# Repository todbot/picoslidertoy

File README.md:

# picoslidertoy

## Table of contents 

- [picoslidertoy](#picoslidertoy)
  - [Table of contents](#table-of-contents)
  - [What is it?](#what-is-it)
  - [Variants](#variants)
  - [Parts needed](#parts-needed)
  - [Soldering components](#soldering-components)
  - [Firmware installation / Installing apps](#firmware-installation--installing-apps)
    - [CircuitPython apps](#circuitpython-apps)
    - [Ready-to-go UF2 file](#ready-to-go-uf2-file)
    - [Installing by hand](#installing-by-hand)
  - [Why?](#why)
    - [What makes it special?](#what-makes-it-special)
    - [Press links](#press-links)

## What is it?
[picoslidertoy](https://github.com/todbot/picoslidertoy) is a touch-sensitive 
control surface that uses 24 GPIO pins of the Raspberry Pi Pico to provide:

- three linear sliders
- two rotary sliders
- nine buttons
- all capacitive touch 

It also includes a cutout for a reverse-mounted SSD1306 I2C OLED display. The Raspberry Pi Pico SMD mounts to the back of the board to provide a clean look for the touch surface.  The entire PCB is 165 mm x 76 mm (6.5" x 3.0").

The picoslidertoy can be a USB MIDI control surface, a USB Macropad keyboard with "analog" controls, or even a USB gamepad.  It can be programmed in [CircuitPython](https://circuitpython.org/) and [`touchio`](https://docs.circuitpython.org/en/latest/shared-bindings/touchio/index.html) or Arduino with my [`TouchyTouch library`](https://github.com/todbot/TouchyTouch).  Several example firmware apps are provided.

## Variants

There are two versions of the picoslidertoy available:

- black PCB -- production version with proper alignment of the cutout for standard 0.96" I2C OLED, comes with all SMD resistors soldered down  Note: the silkscreen on the back has a typo, saying `0.91" I2C OLED`. 

- green PCB -- prototype version with no components soldered down and where the I2C OLED display cutout is a little off. Still usable, or mount the display on the face. 

There is also a nice minimal 3d-printable enclosure available in the github repo (and visible in the photos above).  You really want a case for capacitive touch projects like this to reduce spurious readings. 

## Parts needed

In addition to the [picoslidertoy PCB](https://www.tindie.com/products/todbot/picoslidertoy-capsense-controller-for-pico/), you will need:

- Raspberry Pi Pico 
  - Must be w/ castellated pads & w/o headers,  ([like this](https://amzn.to/4d0KFZC))
  - For USB-C, consider this [USB-C 16 MB Pico clone](https://www.aliexpress.us/item/3256804731684211.html)
  - **(NOTE: NOT the Pico2, since its RP2350 chip has a hardware error)**

- I2C OLED display SSD1306 
   - 0.96" 128 x 64 pixels, in white
   - Pins must be in GND,VCC,SCL,SDA order 
   - Prefer the 27.5 mm wide displays over the 25 mm wide ones ([one example](https://amzn.to/3KDmy73))

- (If you have a green proto one, you will also need 24 x 1M 0603 resistors and 2 x 10k 0603 resistors)

- [3d printed case](./enclosure/picoslidertoy_case.stl) or M2.5 standoffs/screws or some other feet

## Soldering components

- **Pico**  -- the Pico is soldered down surface-mount style, using its castellated pads. 
  [This video soldering a Pico on picotouch](https://github.com/todbot/picotouch?tab=readme-ov-file#how-to-solder-the-pico) is how I do it for this board too.  It's technically surface-mount soldering, 
  but the pads are bigger than most through-hole pads and easy to solder to. 
  Note that Pico clones that don't have castellated pads like the real Pico will
  not work. 
  ([Youtube video with Pico SMD soldering tips](https://www.youtube.com/watch?v=dW9LiOq3Dso "Pico SMD soldering"))

- **OLED Display** -- the display can either be mounted on the front (especially easy if your display's pins
  come pre-soldered) or from the back (my preference).  If mounting from the back, you first need to 
  desolder the 4-pin header on the display and mount a new 4-pin header "reverse" so that pins stick up
  from the front of the display. The main header body is still on the back of the display. 
  (The video below hopefully makes this clearer).  When soldering, do one pin first and check alignment,
  then solder the rest of the pins. Finish up by trimming the excess header pins. 
  ([Youtube video with picoslidertoy soldering tips](https://www.youtube.com/watch?v=zxt3xpre2Vg))

## Firmware installation / Installing apps

### CircuitPython apps

These are the apps currently available 
- [hwtest](https://github.com/todbot/picoslidertoy/blob/main/circuitpython/hwtest/code.py)
    -- a simple on/off test of the touch sensors, no display needed. Use serial REPL to see results

- [hwtest display](https://github.com/todbot/picoslidertoy/blob/main/circuitpython/hwtest_display/code.py) -- like `hwtest` but also outputs simple feedback via the display
 
- [midi_sliders](https://github.com/todbot/picoslidertoy/blob/main/circuitpython/midi_sliders/) -- MIDI controller where the sliders emit CCs and the buttons send NoteOn/NoteOffs

If you've never used a Pico or CircuitPython, there are several ways to put code on it. 
The two main ways I'll present here are:

- Ready-to-go UF2 file in "Releases" 
- Installing by hand:  CircuitPython, code.py, libraries 

### Ready-to-go UF2 file

Steps to install a UF2 file:

- Download a ready-to-go UF2 file from the [Releases section](https://github.com/todbot/picoslidertoy/releases) section
- Hold the BOOTSEL button on the picoslidertoy's Pico while plugging it into your computer
- Copy the UF2 file to the "RPI-RP2" Pico bootloader drive 
- Wait for a bit, then app is running!

In general, I'll try to make UF2 files available in the [Releases section](https://github.com/todbot/picoslidertoy/releases) for the different apps.

### Installing by hand 

Steps to install by hand: 

- Download this repo, either with a `git clone` or clicking on "Code / Download ZIP"
- Download the latest CircuitPython UF2 for Pico at https://circuitpython.org/board/raspberry_pi_pico/
- Install the CircuitPython UF2 (like in the above UF2 steps)
- Wait for CircuitPython to come up and present a CIRCUITPY drive
- Copy the files of the picoslidertoy app in question to CIRCUITPY:

  e.g. for `midi_sliders`, copy `code.py`, `slider_display.py`, `touchslider.py` to CIRCUITPY
  ```
  cp circuitpython/midi_sliders/* /Volumes/CIRCUITPY  # (if macos)
  ```
   
- Install CircuitPython libraries onto Pico

    If you have Python on your computer you can do:
    ```
    pip3 install circup
    circup install adafruit_midi adafruit_displayio_ssd1306 adafruit_hid
    ```
    Otherwise, download the [CircuitPython Libraries Bundle](https://circuitpython.org/libraries)
    and copy over the `adafruit_midi`, `adafruit_displayio_ssd1306` and `adafruit_hid` libraries to
    the `CIRCUITPY/lib` folder on the Pico.

## Why?

I wanted a way to experiment with linear and rotary touch sliders.  I made some [touchwheels](https://github.com/todbot/touchwheels) to give away for Hackaday Supercon 2023 and they were popular. I wanted a larger playground for experimenting with these controls. 

### What makes it special?

The 24 capacitive touch sensors are read directly by the Pico, either via CircuitPython's `touchio` library or the `TouchyTouch` Arduino library.  No external touch chip needed.  I think that's really cool!  Getting an "analog" value out of the three touch sensors that make up a linear or rotary touch slider is fairly simple but there are some tricks I'm developing to make the values stable.

picoslidertoy is also completely open source with schematic files in KiCad and software in CircuitPython and Arduino.

### Press links

- [Adafruit Show-N-Tell Live show 10 Apr 2024](https://www.youtube.com/live/9aliKuS8NTw?si=FC51cfeyoLF2YsNm&t=1055)
- [Hackster.io 11 Apr 2024 article](https://www.hackster.io/news/tod-kurt-s-picoslidertoy-delivers-25-capacitive-touch-inputs-to-a-raspberry-pi-pico-with-sliders-368dca30f01c)

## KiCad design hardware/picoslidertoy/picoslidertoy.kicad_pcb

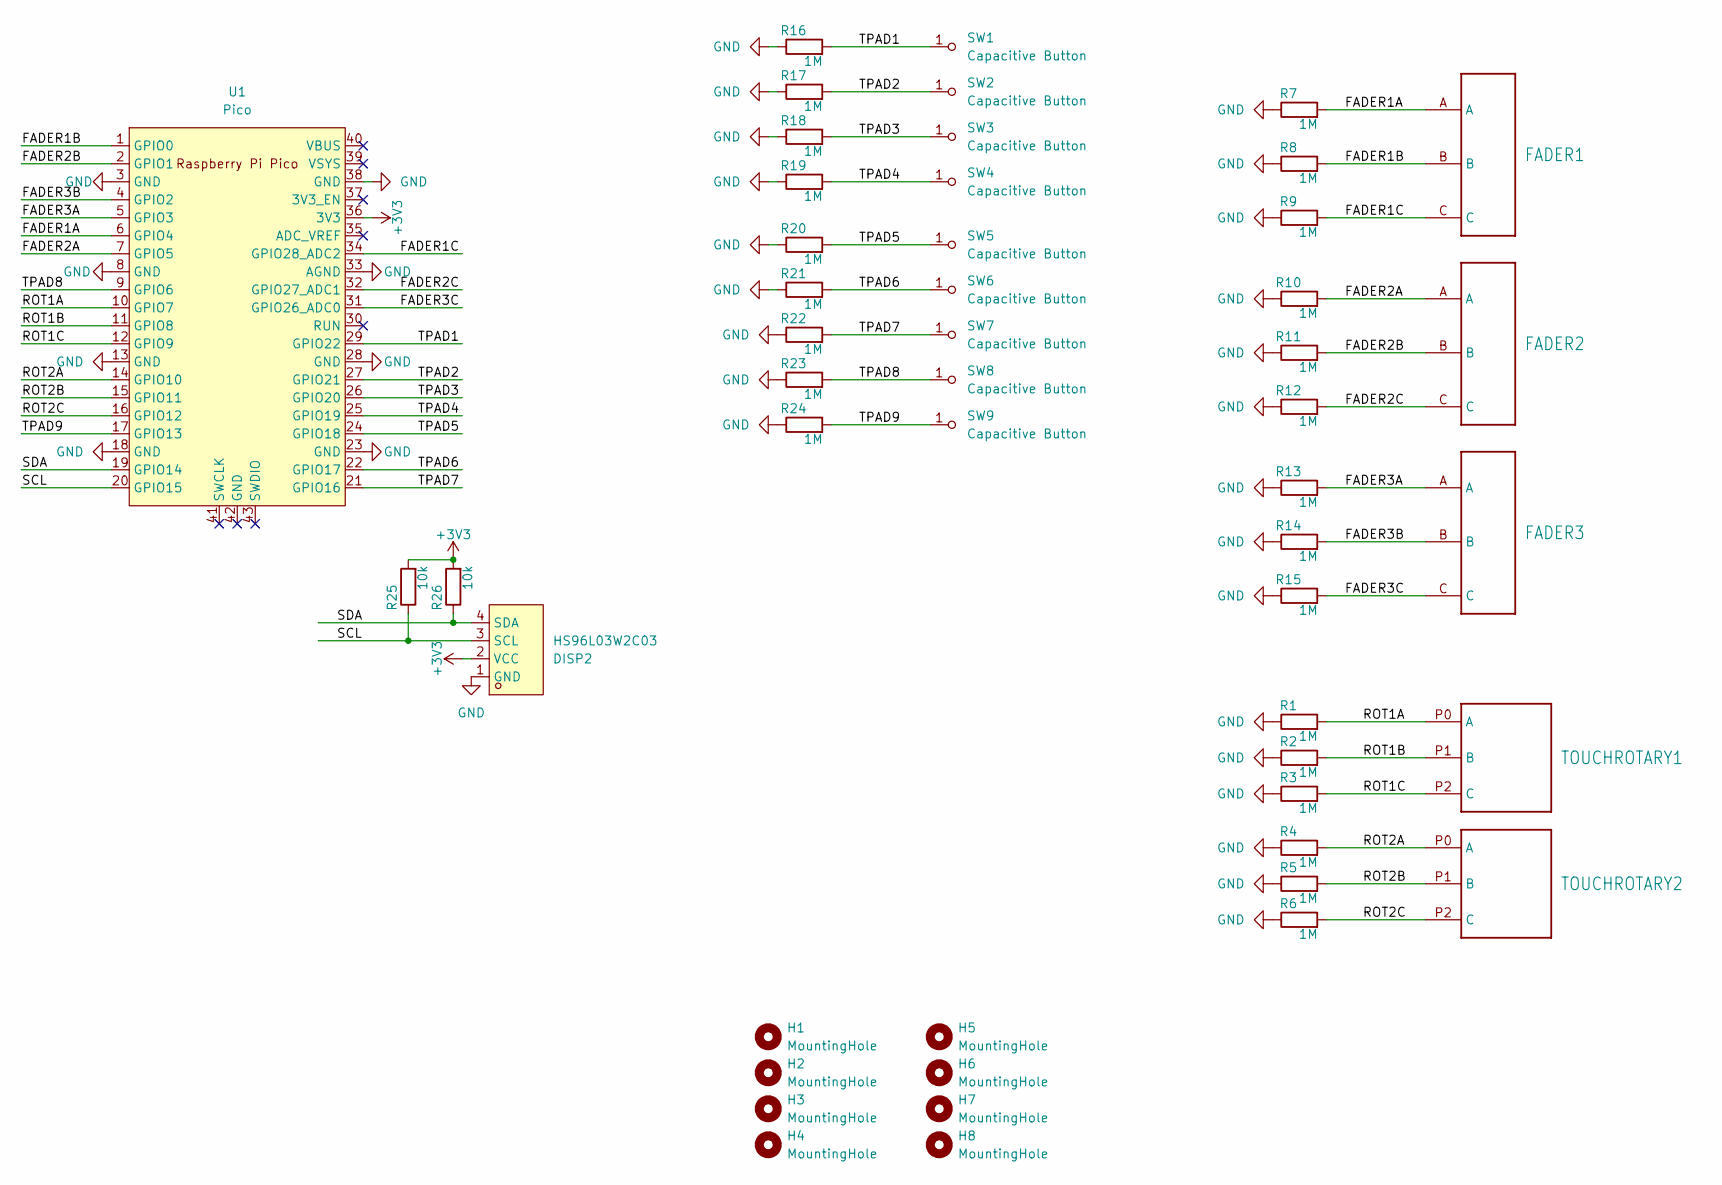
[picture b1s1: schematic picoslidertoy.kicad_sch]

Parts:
DISP2: HS96L03W2C03; OLED-TH_under_fixed_L27.8-W27.2-P2.54_C9900033791; LCSC Part C5248080
FADER1, FADER2, FADER3: TOUCHSLIDER3_8x40B
H1, H2: MountingHole; MountingHole_2.7mm_M2.5_ISO14580
H3, H4: MountingHole; MountingHole_2.7mm_M2.5
H5, H7, H8: MountingHole; MountingHole_2.5mm
H6: MountingHole; MountingHole_2.7mm
R1, R2, R3, R4, R5, R6, R7, R8, R9, R10, R11, R12, R13, R14, R15, R16, R17, R18, R19, R20, R21, R22, R23, R24: 1M; R_0603_1608Metric
R25, R26: 10k; R_0603_1608Metric
SW1, SW2, SW3, SW4, SW5, SW6, SW7, SW8, SW9: Capacitive Button; Pad-CapacitiveTouch
TOUCHROTARY1, TOUCHROTARY2: TOUCHROTARY1B
U1: Pico; RPi_Pico_SMD

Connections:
+3V3: DISP2.2 (VCC), R25.2, R26.2, U1.36 (3V3); also elsewhere on the board
/FADER1A: FADER1.A, R7.2, U1.6 (GPIO4)
/FADER1B: FADER1.B, R8.2, U1.1 (GPIO0)
/FADER1C: FADER1.C, R9.2, U1.34 (GPIO28_ADC2)
/FADER2A: FADER2.A, R10.2, U1.7 (GPIO5)
/FADER2B: FADER2.B, R11.2, U1.2 (GPIO1)
/FADER2C: FADER2.C, R12.2, U1.32 (GPIO27_ADC1)
/FADER3A: FADER3.A, R13.2, U1.5 (GPIO3)
/FADER3B: FADER3.B, R14.2, U1.4 (GPIO2)
/FADER3C: FADER3.C, R15.2, U1.31 (GPIO26_ADC0)
/ROT1A: R1.2, TOUCHROTARY1.P0 (A), U1.10 (GPIO7)
/ROT1B: R2.2, TOUCHROTARY1.P1 (B), U1.11 (GPIO8)
/ROT1C: R3.2, TOUCHROTARY1.P2 (C), U1.12 (GPIO9)
/ROT2A: R4.2, TOUCHROTARY2.P0 (A), U1.14 (GPIO10)
/ROT2B: R5.2, TOUCHROTARY2.P1 (B), U1.15 (GPIO11)
/ROT2C: R6.2, TOUCHROTARY2.P2 (C), U1.16 (GPIO12)
/SCL: DISP2.3 (SCL), R25.1, U1.20 (GPIO15); also elsewhere on the board
/SDA: DISP2.4 (SDA), R26.1, U1.19 (GPIO14); also elsewhere on the board
/TPAD1: R16.2, SW1.1 (A), U1.29 (GPIO22)
/TPAD2: R17.2, SW2.1 (A), U1.27 (GPIO21)
/TPAD3: R18.2, SW3.1 (A), U1.26 (GPIO20)
/TPAD4: R19.2, SW4.1 (A), U1.25 (GPIO19)
/TPAD5: R20.2, SW5.1 (A), U1.24 (GPIO18)
/TPAD6: R21.2, SW6.1 (A), U1.22 (GPIO17)
/TPAD7: R22.2, SW7.1 (A), U1.21 (GPIO16)
/TPAD8: R23.2, SW8.1 (A), U1.9 (GPIO6)
/TPAD9: R24.2, SW9.1 (A), U1.17 (GPIO13)
GND: DISP2.1 (GND), R1.1, R2.1, R3.1, R4.1, R5.1, R6.1, R7.1, R8.1, R9.1, R10.1, R11.1, R12.1, R13.1, R14.1, R15.1, R16.1, R17.1, R18.1, R19.1, R20.1, R21.1, R22.1, R23.1, R24.1, U1.3 (GND), U1.8 (GND), U1.13 (GND), U1.18 (GND), U1.23 (GND), U1.28 (GND), U1.33 (AGND), U1.38 (GND); also elsewhere on the board

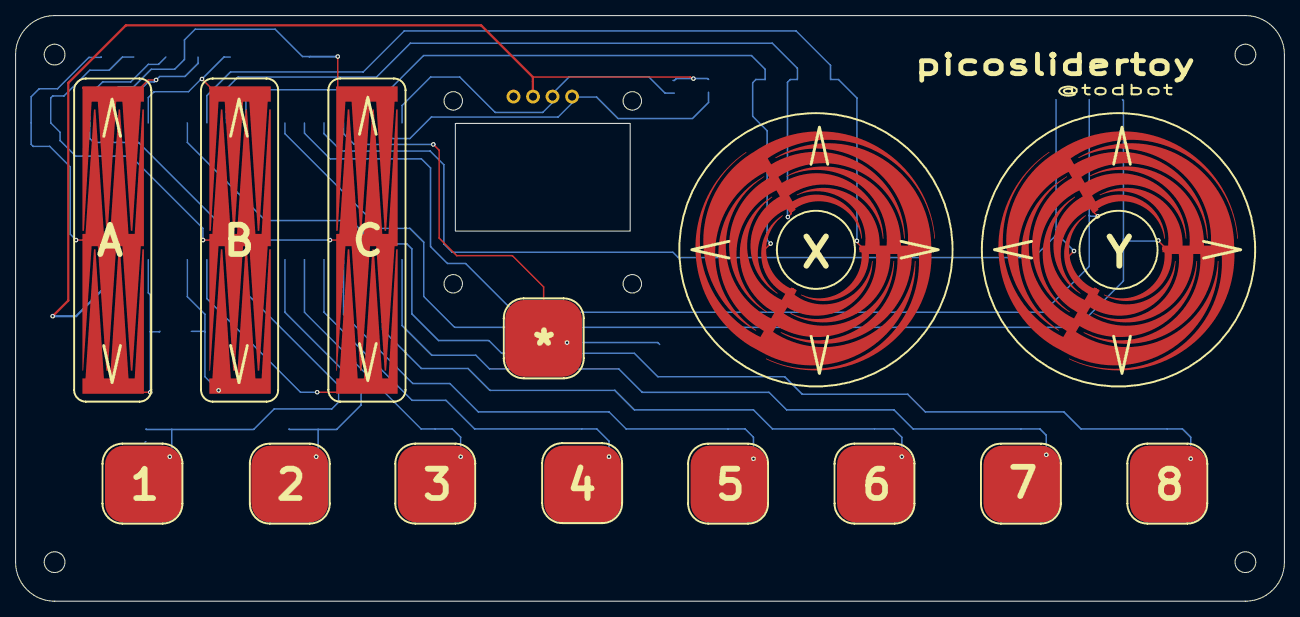
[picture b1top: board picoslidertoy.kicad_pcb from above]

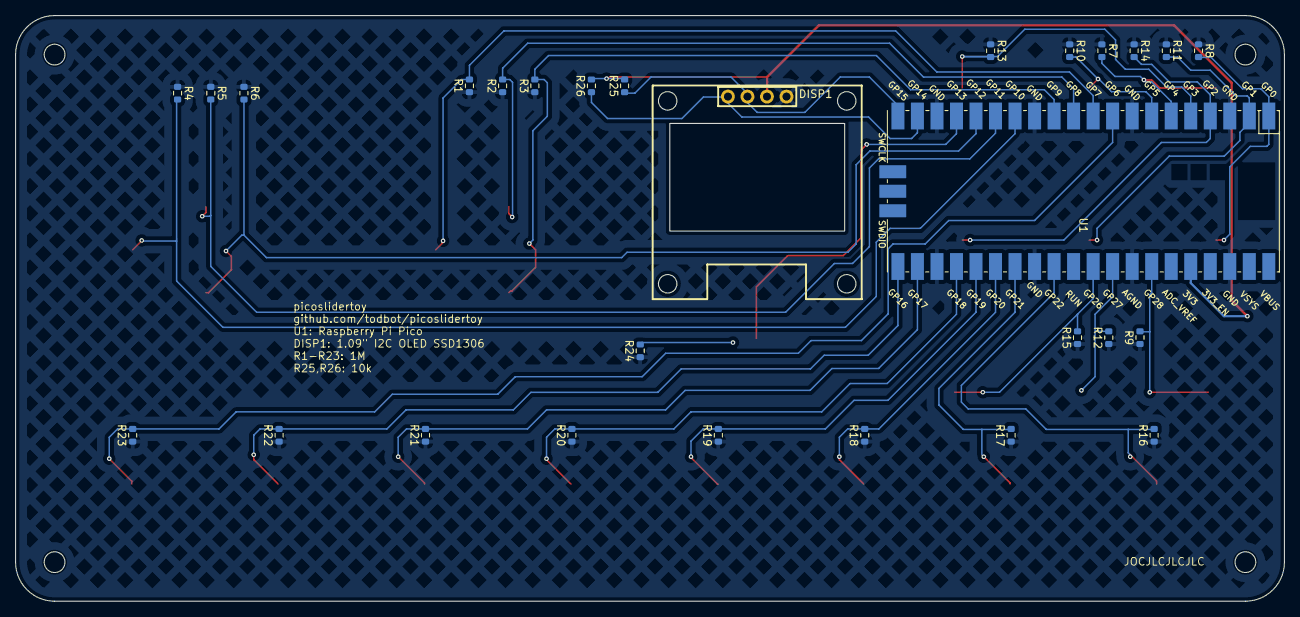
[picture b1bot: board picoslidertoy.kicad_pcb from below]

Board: 2 copper layers, 165.1 x 76.2 mm, 46 parts (27 on the bottom side), 28 nets.

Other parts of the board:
DISP1: HS96L03W2C03; OLED-TH_under_fixed_L27.8-W27.2-P2.54_C9900033791

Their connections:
+3V3: DISP1.2 (VCC); also elsewhere on the board
/SCL: DISP1.3 (SCL); also elsewhere on the board
/SDA: DISP1.4 (SDA); also elsewhere on the board
GND: DISP1.1 (GND); also elsewhere on the board

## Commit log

2024-03-16 hardware reimplemented in kicad from eagle version, zero unrouted but drc errors
2024-03-16 pcb fixes
2024-03-16 pcb silksreen
2024-03-17 pcb proto submitted to fab
2024-03-23 circuitpython hwtest
2024-03-23 circuitpython slider_test as in picoslider prototype demo video, save proto1 pcb as own kicad project
2024-03-23 add render
2024-03-24 fix display knob bounds
2024-03-25 circuitpython midi_sliders demo
2024-03-29 midi_slider small tuning
2024-03-29 pcb display positioning tune
2024-03-30 pcb display position tuning
2024-04-10 added enclosure stl, small reorg
2024-04-11 add scale to circuitpython midi_sliders
2024-04-11 add more README, photos, other docs
2024-04-14 readme: fix 25 -> 24 typo
2024-04-15 readme: added some soldering tips
2024-04-15 readme: add toc
2024-04-16 fix typo
2024-04-16 update readme with apps info, new display hole-less version
2024-04-16 fix toc
2024-04-16 new display hole-less pcb to fab
2024-04-16 cleanup
2024-04-16 add link to enclosure
2024-06-05 add boot.py for CirPy 9.1+ for useful midi port names
2025-04-11 Copy midi_sliders example
2025-04-11 Initial build of hid controller with hot key and media modes
2025-04-15 Move `hid_sliders` into separate examples, `hid_hotkeys` and `hid_media`.
2025-04-15 Remove `adafruit_display_text` dependency.
